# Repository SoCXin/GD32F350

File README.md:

# [GD32F350](https://github.com/SoCXin/GD32F350)

* [GigaDevice](https://www.st.com/zh/)：[Cortex-M4](https://github.com/SoCXin/Cortex)
* [L4R4](https://github.com/SoCXin/Level) ：108 MHz * 1.25 DMIPS/MHz (285CoreMark)

## [简介](https://github.com/SoCXin/GD32F350/wiki)

[GD32F350](https://github.com/SoCXin/GD32F350) 系列

### 关键特性

* USB FS

#### 封装规格

* QFN28/32
* LQFP64/48

### [资源收录](https://github.com/SoCXin)

* [参考文档](docs/)
* [参考资源](src/)
* [参考工程](project/)

### [选型建议](https://github.com/SoCXin)

[GD32F350](https://github.com/SoCXin/GD32F350)

### [探索芯世界 www.SoC.xin](http://www.SoC.Xin)

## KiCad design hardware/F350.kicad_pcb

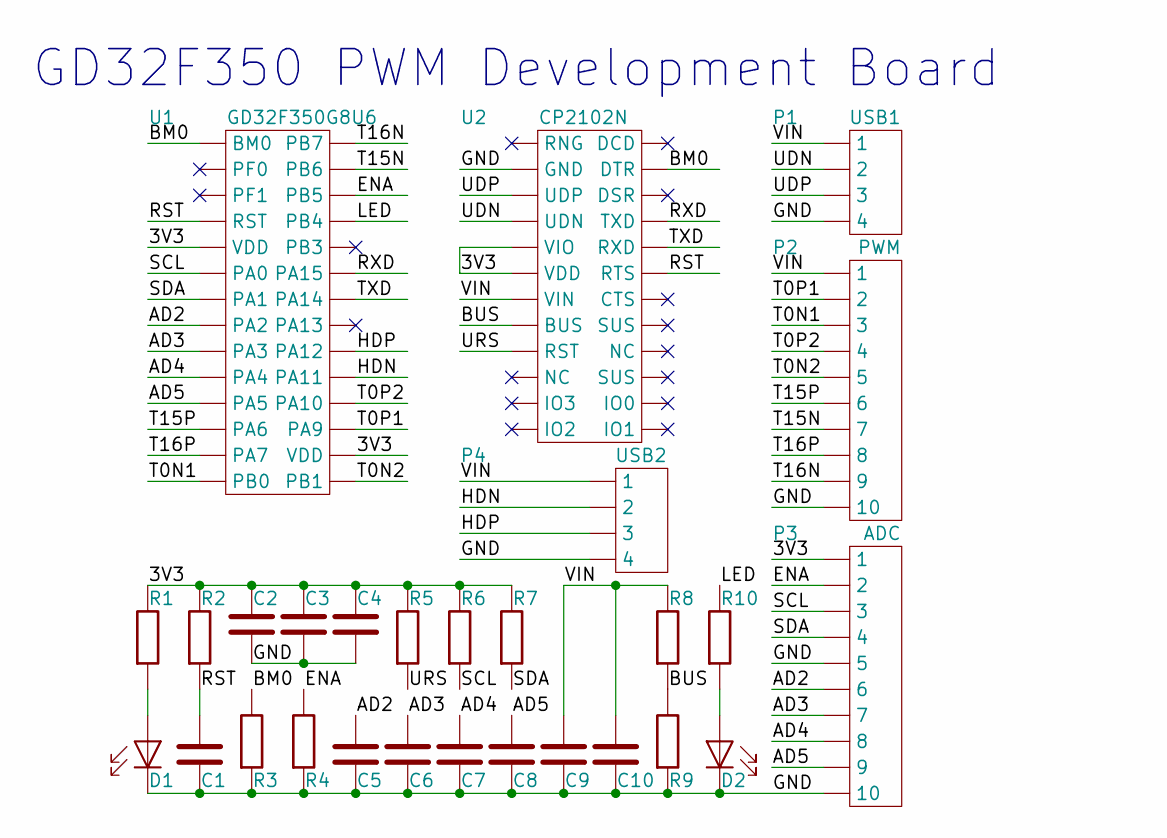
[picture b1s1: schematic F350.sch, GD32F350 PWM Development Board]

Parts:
C1, C2, C3, C4, C5, C6, C7, C8, C9, C10: Capacitor; 0402
D1, D2: LED; 0402
P1: USB1; U253-051T
P2: PWM; HDR1X10
P3: ADC; HDR1X10
P4: USB2; U253-051T
R1, R2, R3, R4, R5, R6, R7, R8, R9, R10: Resistor; 0402
U1: GD32F350G8U6; QFN28_4,0_4.0_0.4
U2: CP2102N; QFN24_4.0_4.0_0.5

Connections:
/3V3: C2.1, C3.1, C4.1, P3.1, R1.1, R2.1, R5.1, R6.1, R7.1, U1.5 (VDD), U1.16 (VDD), U2.5 (VIO), U2.6 (VDD)
/AD2: C5.1, P3.6, U1.8 (PA2)
/AD3: C6.1, P3.7, U1.9 (PA3)
/AD4: C7.1, P3.8, U1.10 (PA4)
/AD5: C8.1, P3.9, U1.14 (PA5)
/BM0: R3.1, U1.1 (BM0), U2.23 (DTR)
/BUS: R8.2, R9.1, U2.8 (BUS)
/ENA: P3.2, R4.1, U1.26 (PB5)
/GND: C1.2, C2.2, C3.2, C4.2, C5.2, C6.2, C7.2, C8.2, C9.2, C10.2, D1.2 (K), D2.2 (K), P1.4, P2.10, P3.5, P3.10, P4.4, R3.2, R4.2, R9.2, U2.2 (GND)
/HDN: P4.2, U1.19 (PA11)
/HDP: P4.3, U1.20 (PA12)
/LED: R10.1, U1.25 (PB4)
/RST: C1.1, R2.2, U1.4 (RST), U2.19 (RTS)
/RXD: U1.23 (PA15), U2.21 (TXD)
/SCL: P3.3, R6.2, U1.6 (PA0)
/SDA: P3.4, R7.2, U1.7 (PA1)
/T0N1: P2.3, U1.11 (PB0)
/T0N2: P2.5, U1.15 (PB1)
/T0P1: P2.2, U1.17 (PA9)
/T0P2: P2.4, U1.18 (PA10)
/T15N: P2.7, U1.27 (PB6)
/T15P: P2.6, U1.13 (PA6)
/T16N: P2.9, U1.28 (PB7)
/T16P: P2.8, U1.12 (PA7)
/TXD: U1.22 (PA14), U2.20 (RXD)
/UDN: P1.2, U2.4 (UDN)
/UDP: P1.3, U2.3 (UDP)
/URS: R5.2, U2.9 (RST)
/VIN: C9.1, C10.1, P1.1, P2.1, P4.1, R8.1, U2.7 (VIN)
unnamed: D1.1 (A), R1.2
unnamed: D2.1 (A), R10.2

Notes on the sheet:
GD32F350 PWM Development Board

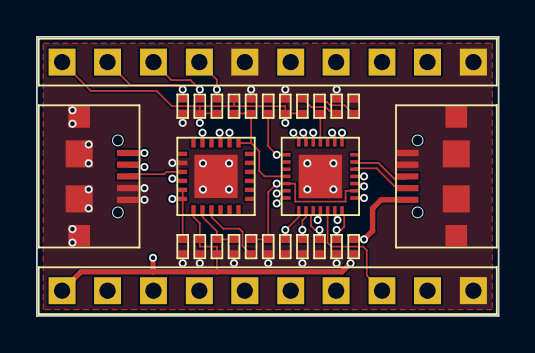
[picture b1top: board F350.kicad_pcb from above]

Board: 4 copper layers, 25.6 x 15.5 mm, 28 parts (0 on the bottom side), 31 nets.

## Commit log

2020-10-16 init
2020-10-16 add docs
2020-11-30 add src
2020-11-30 add lib src
2021-05-25 add kicad
